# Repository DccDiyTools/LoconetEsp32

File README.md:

# LoconetEsp32
Esp32 Loconet Interface
# LocoBuffer from LocoLinx32U4

Board for use wiht the [https://github.com/mrrwa/LocoNet/tree/master/examples/LocoLinx32U4] code, there is a copy on this repository for platform.io .

# 0.0.1
- [x] USB
- [x] Loconet
- [x] Leds loconet
- [x] ESP32
- [ ] Btn Reset

# 0.0.X
- [] Loconet Power 
- [] Loconet Master
- [] USB-C
- [] Non-Inv TX
- [] SD
- [] BTN AP
- [] Led Wifi RGB

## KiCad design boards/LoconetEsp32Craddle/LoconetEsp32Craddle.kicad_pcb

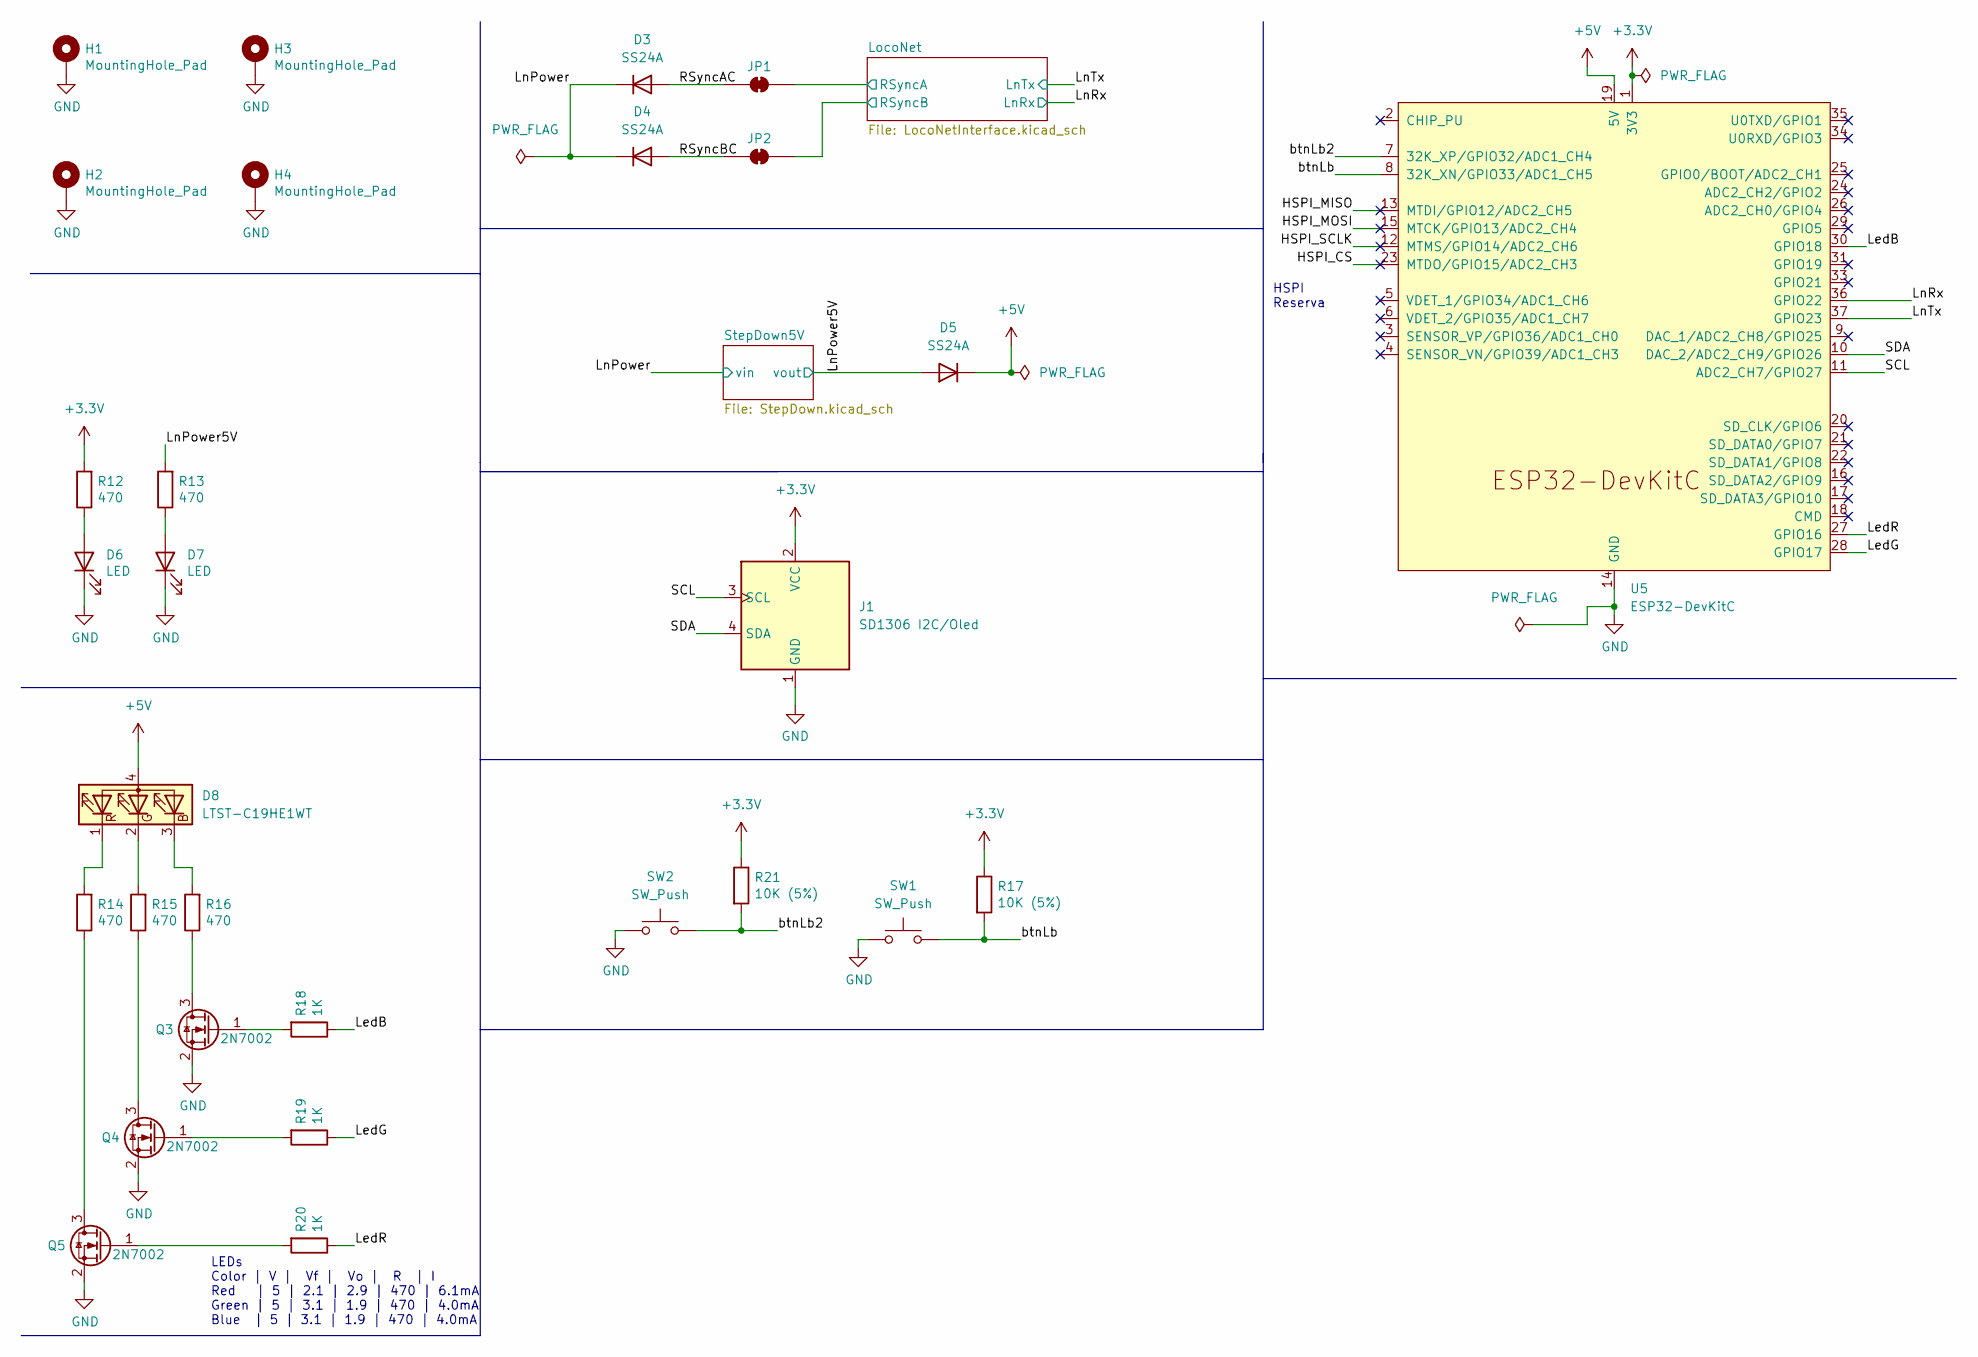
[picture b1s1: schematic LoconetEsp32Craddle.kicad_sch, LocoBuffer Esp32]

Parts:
D3, D4, D5: SS24A; D_SMA; LCSC C95872
D6, D7: LED; LED_0805_2012Metric; LCSC C2296
D8: LTST-C19HE1WT; LED_LiteOn_LTST-C19HE1WT; LCSC C458749
H1, H2, H3, H4: MountingHole_Pad; MountingHole_3.2mm_M3_ISO7380_Pad
J1: SD1306 I2C/Oled; ER_OLEDM0.91_1x-I2C-128x64OLED
JP1, JP2: SolderJumper_2_Bridged; SolderJumper-2_P1.3mm_Bridged2Bar_RoundedPad1.0x1.5mm
Q3, Q4, Q5: 2N7002; SOT-23; LCSC C8545
R12, R13, R14, R15, R16: 470; R_0805_2012Metric; LCSC C17710
R17, R21: 10K (5%); R_0805_2012Metric; LCSC C17414
R18, R19, R20: 1K; R_0805_2012Metric; LCSC C17513
SW1, SW2: SW_Push; SW_SPST_CK_RS282G05A3
U5: ESP32-DevKitC

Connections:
+3.3V: J1.2 (VCC), R12.2, R17.1, R21.1, U5.1 (3V3); also elsewhere on the board
+5V: D5.1 (K), D8.4 (A), U5.19 (5V)
/HSPI_CS: U5.23 (MTDO/GPIO15/ADC2_CH3)
/HSPI_MISO: U5.13 (MTDI/GPIO12/ADC2_CH5)
/HSPI_MOSI: U5.15 (MTCK/GPIO13/ADC2_CH4)
/HSPI_SCLK: U5.12 (MTMS/GPIO14/ADC2_CH6)
/LedB: R18.1, U5.30 (GPIO18)
/LedG: R19.1, U5.28 (GPIO17)
/LedR: R20.1, U5.27 (GPIO16)
/LnPower: D3.1 (K), D4.1 (K); also elsewhere on the board
/LnPower5V: D5.2 (A), R13.2; also elsewhere on the board
/LnRx: U5.36 (GPIO22); also elsewhere on the board
/LnTx: U5.37 (GPIO23); also elsewhere on the board
/LocoNet/RSyncA: JP1.2 (B); also elsewhere on the board
/LocoNet/RSyncB: JP2.2 (B); also elsewhere on the board
/RSyncAC: D3.2 (A), JP1.1 (A)
/RSyncBC: D4.2 (A), JP2.1 (A)
/SCL: J1.3 (SCL), U5.11 (ADC2_CH7/GPIO27)
/SDA: J1.4 (SDA), U5.10 (DAC_2/ADC2_CH9/GPIO26)
/btnLb: R17.2, SW1.2, U5.8 (32K_XN/GPIO33/ADC1_CH5)
/btnLb2: R21.2, SW2.2, U5.7 (32K_XP/GPIO32/ADC1_CH4)
GND: D6.1 (K), D7.1 (K), H1.1 (1_1), H2.1 (1_1), H3.1 (1_1), H4.1 (1_1), J1.1 (GND), Q3.2 (S), Q4.2 (S), Q5.2 (S), SW1.1, SW2.1, U5.14 (GND), U5.32 (GND), U5.38 (GND); also elsewhere on the board
unnamed: D6.2 (A), R12.1
unnamed: D7.2 (A), R13.1
unnamed: D8.3 (BK), R16.2
unnamed: D8.2 (GK), R15.2
unnamed: D8.1 (RK), R14.2
unnamed: Q3.3 (D), R16.1
unnamed: Q3.1 (G), R18.2
unnamed: Q4.3 (D), R15.1
unnamed: Q4.1 (G), R19.2
unnamed: Q5.3 (D), R14.1
unnamed: Q5.1 (G), R20.2

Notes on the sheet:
LEDs Color | V | Vf | Vo | R | I Red | 5 | 2.1 | 2.9 | 470 | 6.1mA Green | 5 | 3.1 | 1.9 | 470 | 4.0mA Blue | 5 | 3.1 | 1.9 | 470 | 4.0mA
HSPI Reserva

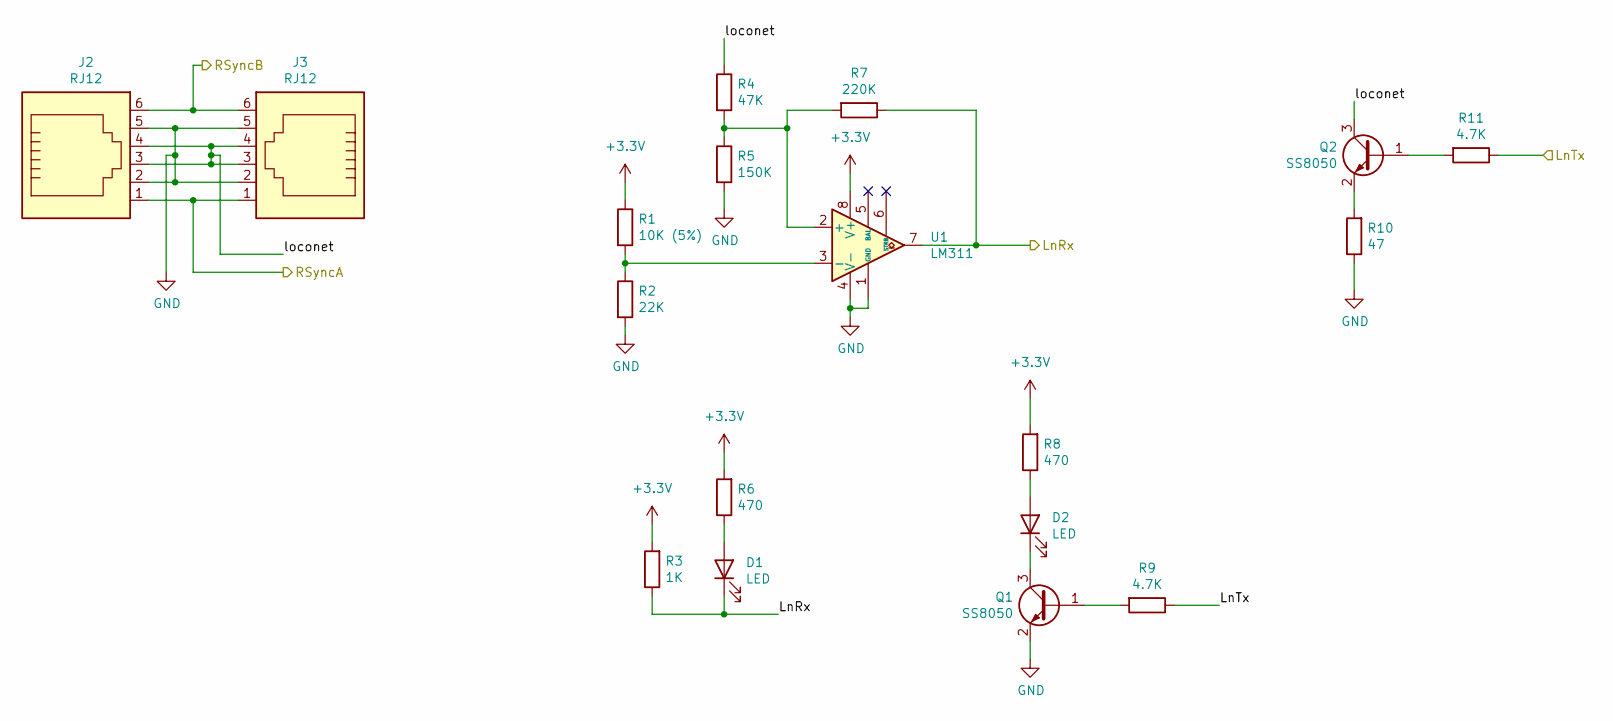
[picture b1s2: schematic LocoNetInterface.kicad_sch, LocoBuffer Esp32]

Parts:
D1, D2: LED; LED_0805_2012Metric; LCSC C2296
J2, J3: RJ12; RJ12_AMPHENOL_RJE0166001
Q1, Q2: SS8050; SOT-23; LCSC C2150
R1: 10K (5%); R_0805_2012Metric; LCSC C17414
R2: 22K; R_0805_2012Metric; LCSC C17560
R3: 1K; R_0805_2012Metric; LCSC C17513
R4: 47K; R_0805_2012Metric; LCSC C17713
R5: 150K; R_0805_2012Metric; LCSC C17470
R6, R8: 470; R_0805_2012Metric; LCSC C17710
R7: 220K; R_0805_2012Metric; LCSC C17556
R9, R11: 4.7K; R_0805_2012Metric; LCSC C229219
R10: 47; R_0805_2012Metric; LCSC C17714
U1: LM311; SOIC-8_3.9x4.9mm_P1.27mm; LCSC C12597

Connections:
+3.3V: R1.1, R3.2, R6.2, R8.2, U1.8 (V+); also elsewhere on the board
/LnRx: D1.1 (K), R3.1, R7.1, U1.7; also elsewhere on the board
/LnTx: R9.1, R11.1; also elsewhere on the board
/LocoNet/RSyncA: J2.1, J3.1; also elsewhere on the board
/LocoNet/RSyncB: J2.6, J3.6; also elsewhere on the board
/LocoNet/loconet: J2.3, J2.4, J3.3, J3.4, Q2.3 (C), R4.1
GND: J2.2, J2.5, J3.2, J3.5, Q1.2 (E), R2.2, R5.2, R10.1, U1.1 (GND), U1.4 (V-); also elsewhere on the board
unnamed: D1.2 (A), R6.1
unnamed: D2.2 (A), R8.1
unnamed: D2.1 (K), Q1.3 (C)
unnamed: Q1.1 (B), R9.2
unnamed: Q2.1 (B), R11.2
unnamed: Q2.2 (E), R10.2
unnamed: R4.2, R5.1, R7.2, U1.2 (+)
unnamed: R1.2, R2.1, U1.3 (-)

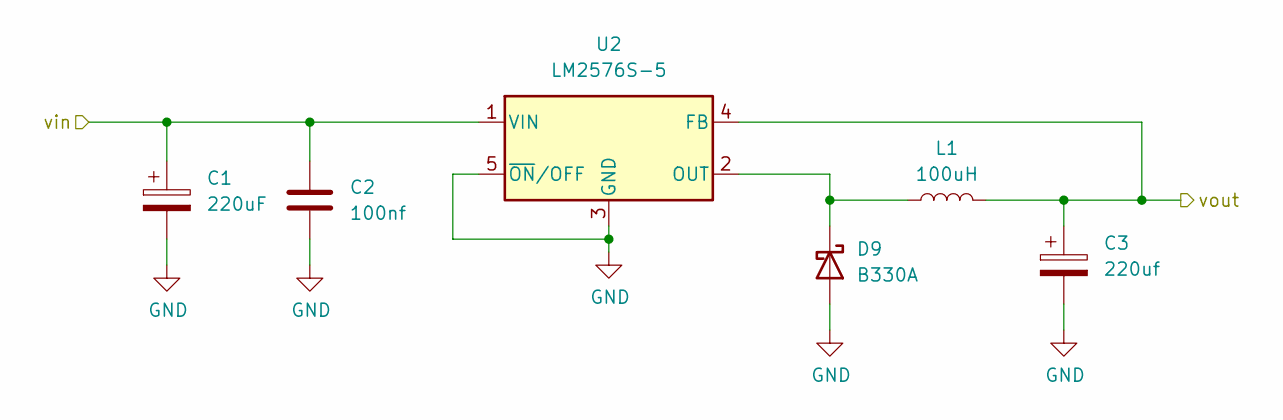
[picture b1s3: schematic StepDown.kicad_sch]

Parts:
C1: 220uF; CP_Elec_8x10.5; LCSC C131124
C2: 100nf; C_0805_2012Metric; LCSC C282732
C3: 220uf; CP_Elec_8x10.5; LCSC C131124
D9: B330A; D_SMA; LCSC C110485
L1: 100uH; L_Sunlord_MWSA1206S-101; LCSC C408533
U2: LM2576S-5; TO-263-5_TabPin3; LCSC C194472

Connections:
/LnPower: C1.1, C2.1, U2.1 (VIN); also elsewhere on the board
/LnPower5V: C3.1, L1.2, U2.4 (FB); also elsewhere on the board
GND: C1.2, C2.2, C3.2, D9.2 (A), U2.3 (GND), U2.5 (~ON/OFF); also elsewhere on the board
unnamed: D9.1 (K), L1.1, U2.2 (OUT)

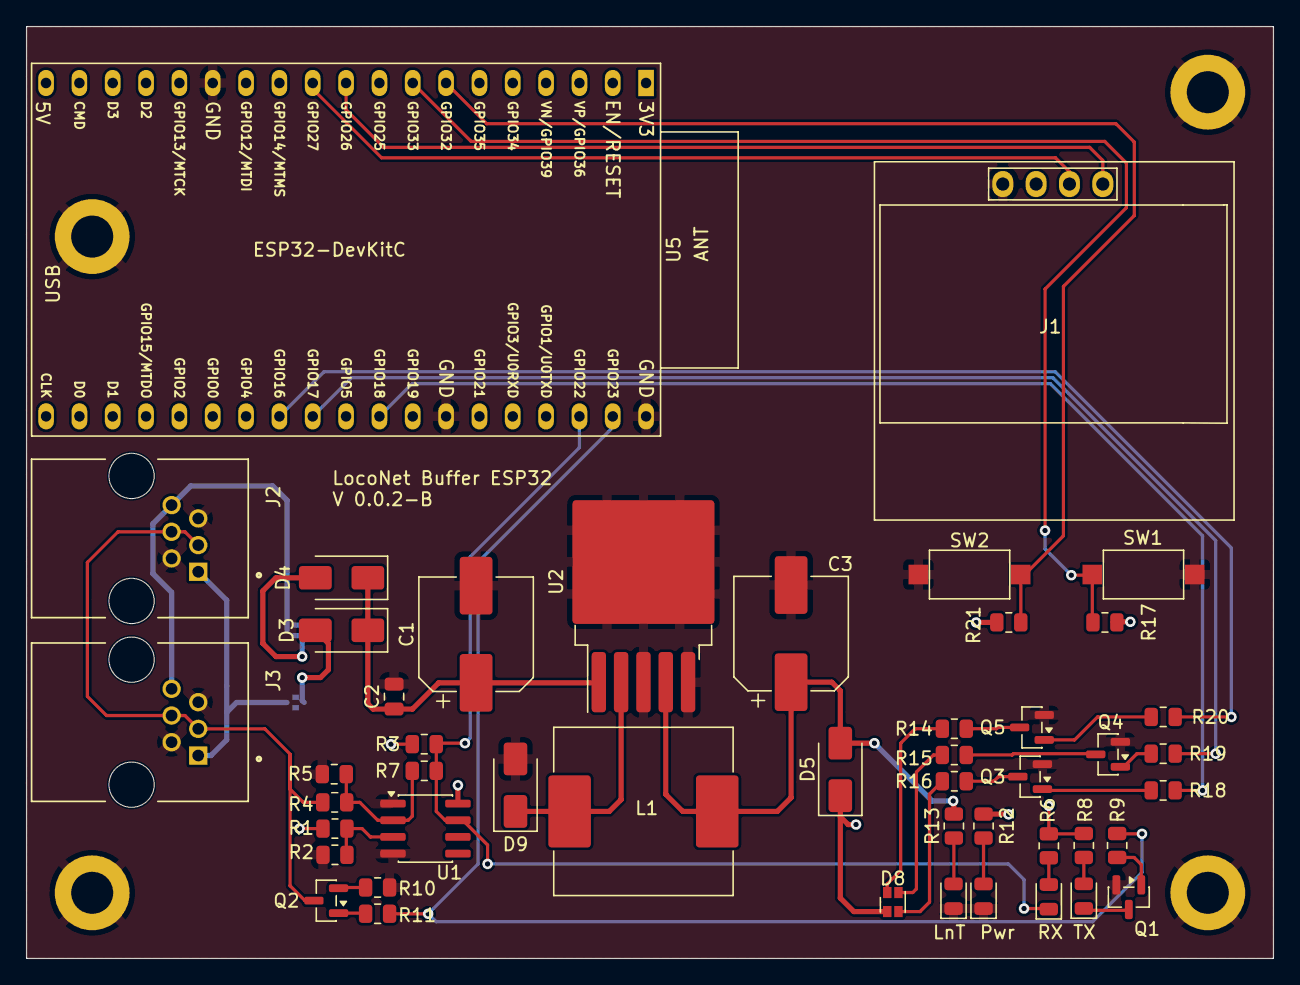
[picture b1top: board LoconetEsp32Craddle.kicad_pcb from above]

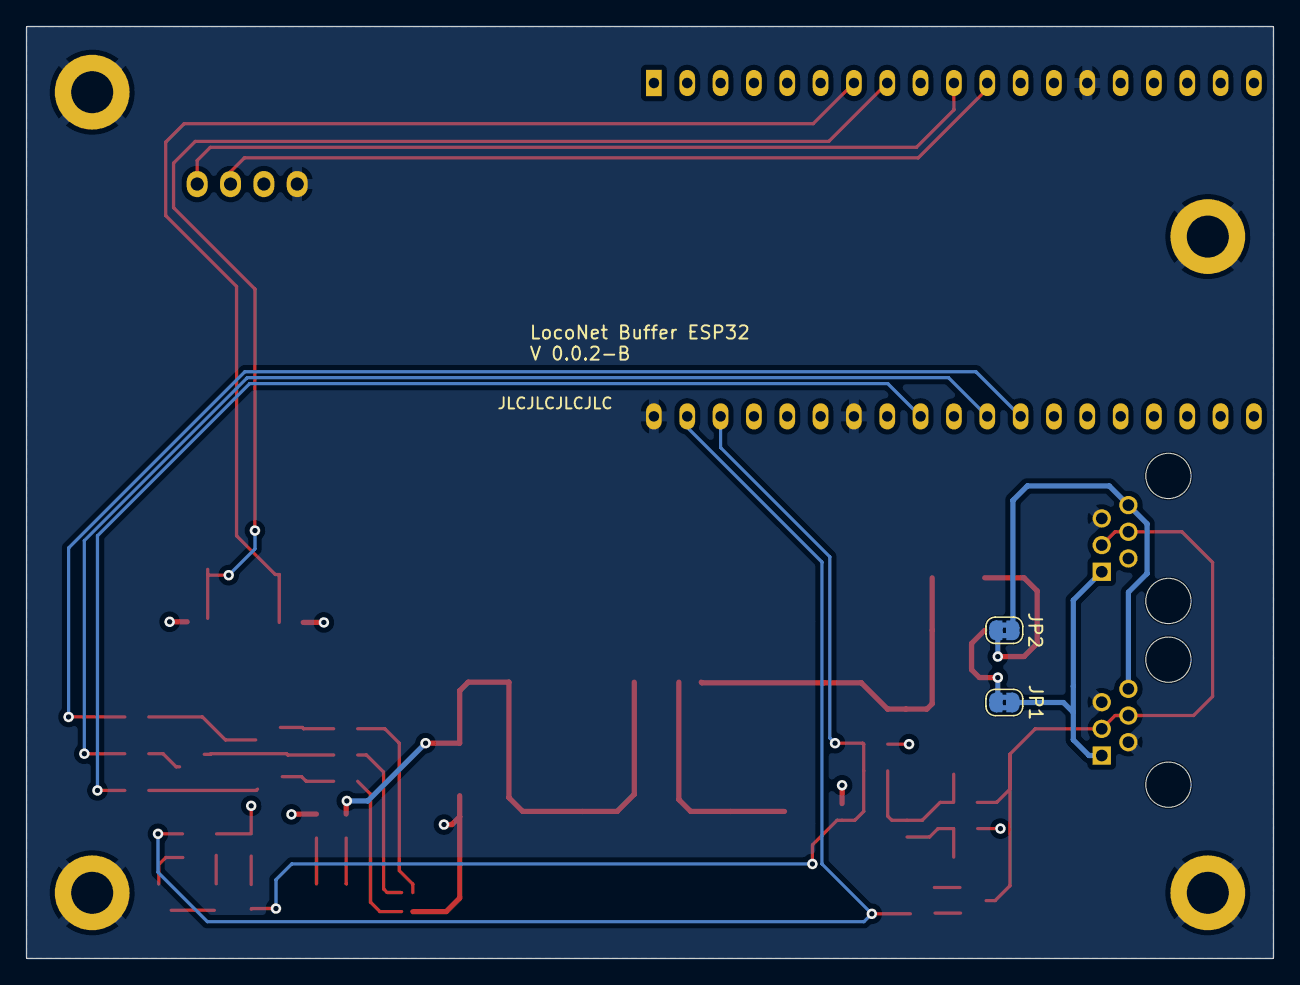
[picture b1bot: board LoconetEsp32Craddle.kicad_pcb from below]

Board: 4 copper layers, 95.0 x 71.0 mm, 53 parts (2 on the bottom side), 39 nets.

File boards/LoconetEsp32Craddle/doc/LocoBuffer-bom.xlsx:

|  | Bill of Materials
 |  | Schematic: | LocoBuffer | Component Groups: | 24
 |  | Variant: | default | Component Count: | 47 (43 SMD/ 4 THT)
 |  | Revision: | 0.0.1 | Fitted Components: | 47 (43 SMD/ 4 THT)
 |  | Date: | 2023-07-17 | Number of PCBs: | 1
 |  | KiCad Version: | 7.0.7-7.0.7~ubuntu23.04.1 | Total Components: | 47
Row | Description | Part | References | Value | Footprint | Quantity Per PCB | Status | Datasheet | LCSC | Sim.Device | Sim.Pins
1 | Unpolarized capacitor | C | C2 | 100nf | C_0805_2012Metric | 1 |  | ~ | C282732
2 | Polarized capacitor | C_Polarized | C1 C3 | 220uF | CP_Elec_8x10.5 | 2 |  | ~ | C131124
3 | 30V 3A Schottky Barrier Rectifier Diode, SMC | B330 | D9 | B330A | D_SMA | 1 |  | http://www.jameco.com/Jameco/Products/ProdDS/1538777.pdf | C110485
4 | Light emitting diode | LED | D1 D2 D6 D7 | LED | LED_0805_2012Metric | 4 |  | ~ | C2296
5 | RGB LED, red/green/blue/anode | LED_RGBA | D8 | LTST-C19HE1WT | LED_LiteOn_LTST-C19HE1WT | 1 |  | ~ | C458749
6 | Diode | D | D3 D4 D5 | SS24A | D_SMA | 3 |  | ~ | C95872 | D | 1=K 2=A
7 | RJ connector, 6P6C (6 positions 6 connected) | RJ12 | J2 J3 | RJ12 | AMPHENOL_RJE0166001 | 2 |  | ~
8 | Generic connector, single row, 01x04, script generated (kicad-library-utils/sch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 | Conn_01x04 | J1 | SD1306 I2C/Oled | 128x64OLED | 1 |  | ~
9 | Inductor | L | L1 | 100uH | L_Sunlord_MWSA1206S-101 | 1 |  | ~ | C408533
10 | 0.115A Id, 60V Vds, N-Channel MOSFET, SOT-23 | 2N7002 | Q3 Q4 Q5 | 2N7002 | SOT-23 | 3 |  | https://www.onsemi.com/pub/Collateral/NDS7002A-D.PDF | C8545
11 | NPN transistor, base/emitter/collector | Q_NPN_BEC | Q1 Q2 | SS8050 | SOT-23 | 2 |  | ~ | C2150
12 | Resistor | R | R10 | 47 | R_0805_2012Metric | 1 |  | ~ | C17714
13 | Resistor | R | R6 R8 R12 R13 R14 R15 R16 | 470 | R_0805_2012Metric | 7 |  | ~ | C17710
14 | Resistor | R | R3 R18 R19 R20 | 1K | R_0805_2012Metric | 4 |  | ~ | C17513
15 | Resistor | R | R9 R11 | 4.7K | R_0805_2012Metric | 2 |  | ~ | C229219
16 | Resistor | R | R2 | 22K | R_0805_2012Metric | 1 |  | ~ | C17560
17 | Resistor | R | R4 | 47K | R_0805_2012Metric | 1 |  | ~ | C17713
18 | Resistor | R | R5 | 150K | R_0805_2012Metric | 1 |  | ~ | C17470
19 | Resistor | R | R7 | 220K | R_0805_2012Metric | 1 |  | ~ | C17556
20 | Resistor | R | R1 R17 R21 | 10K (5%) | R_0805_2012Metric | 3 |  | ~ | C17414
21 | Push button switch, generic, two pins | SW_Push | SW1 SW2 | SW_Push | SW_SPST_CK_RS282G05A3 | 2 |  | ~
22 | Development Kit | ESP32-DevKitC | U5 | ESP32-DevKitC | ESP32-DevKitC | 1 |  | https://docs.espressif.com/projects/esp-idf/zh_CN/latest/esp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
23 | 5V, 3A SIMPLE SWITCHER® Step-Down Voltage Regulator, TO-263 | LM2576S-5 | U2 | LM2576S-5 | TO-263-5_TabPin3 | 1 |  | http://www.ti.com/lit/ds/symlink/lm2576.pdf | C194472
24 | Voltage Comparator, DIP-8/SOIC-8 | LM311 | U1 | LM311 | SOIC-8_3.9x4.9mm_P1.27mm | 1 |  | http://www.ti.com/lit/ds/symlink/lm311.pdf | C12597

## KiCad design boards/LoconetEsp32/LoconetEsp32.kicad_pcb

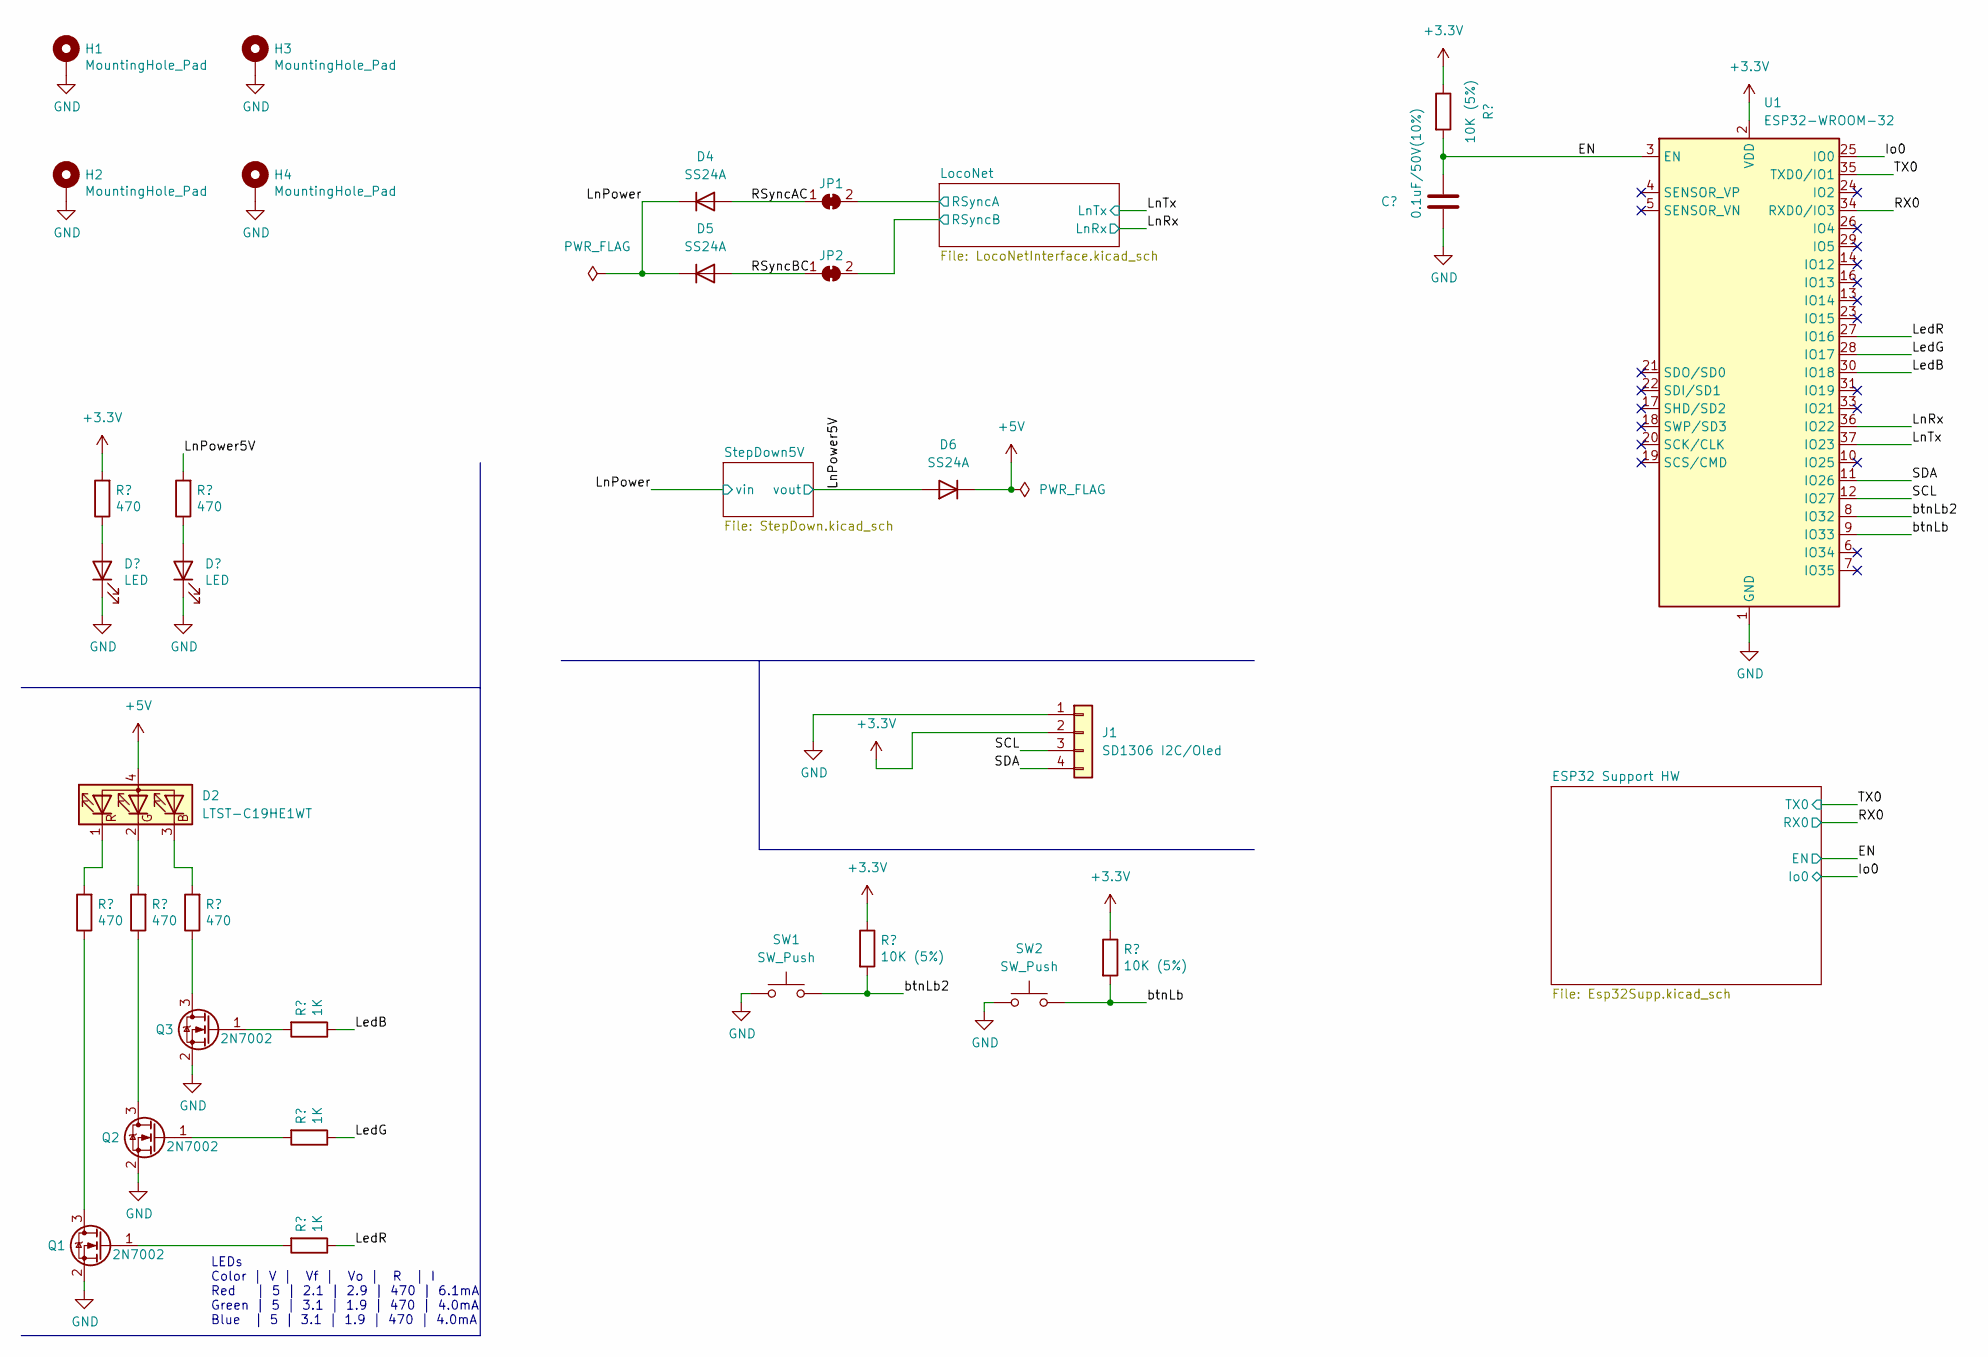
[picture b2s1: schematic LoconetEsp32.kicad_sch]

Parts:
C1: 0.1uF/50V(10%); C_0805_2012Metric; LCSC C49678
D1, D3: LED; LED_0805_2012Metric; LCSC C2296
D2: LTST-C19HE1WT; LED_LiteOn_LTST-C19HE1WT; LCSC C458749
D4, D5, D6: SS24A; D_SMA; LCSC C95872
H1, H2, H3, H4: MountingHole_Pad; MountingHole_3.2mm_M3_ISO7380_Pad
J1: SD1306 I2C/Oled; 128x64OLED
JP1, JP2: SolderJumper_2_Bridged; SolderJumper-2_P1.3mm_Bridged2Bar_RoundedPad1.0x1.5mm
Q1, Q2, Q3: 2N7002; SOT-23; LCSC C8545
R1, R2, R3, R4, R5: 470; R_0805_2012Metric; LCSC C17710
R6, R7, R8: 1K; R_0805_2012Metric; LCSC C17513
R9, R10, R11: 10K (5%); R_0805_2012Metric; LCSC C17414
SW1, SW2: SW_Push; SW_SPST_CK_RS282G05A3
U1: ESP32-WROOM-32; LCSC C701343

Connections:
+3.3V: J1.2, R2.2, R9.1, R10.1, R11.1, U1.2 (VDD); also elsewhere on the board
+5V: D2.4 (A), D6.1 (K); also elsewhere on the board
/EN: C1.1, R11.2, U1.3 (EN); also elsewhere on the board
/Io0: U1.25 (IO0); also elsewhere on the board
/LedB: R6.1, U1.30 (IO18)
/LedG: R7.1, U1.28 (IO17)
/LedR: R8.1, U1.27 (IO16)
/LnPower: D4.1 (K), D5.1 (K); also elsewhere on the board
/LnPower5V: D6.2 (A), R4.2; also elsewhere on the board
/LnRx: U1.36 (IO22); also elsewhere on the board
/LnTx: U1.37 (IO23); also elsewhere on the board
/LocoNet/RSyncA: JP1.2 (B); also elsewhere on the board
/LocoNet/RSyncB: JP2.2 (B); also elsewhere on the board
/RSyncAC: D4.2 (A), JP1.1 (A)
/RSyncBC: D5.2 (A), JP2.1 (A)
/RX0: U1.34 (RXD0/IO3); also elsewhere on the board
/SCL: J1.3, U1.12 (IO27)
/SDA: J1.4, U1.11 (IO26)
/TX0: U1.35 (TXD0/IO1); also elsewhere on the board
/btnLb: R10.2, SW2.2, U1.9 (IO33)
/btnLb2: R9.2, SW1.2, U1.8 (IO32)
GND: C1.2, D1.1 (K), D3.1 (K), H1.1, H2.1, H3.1, H4.1, J1.1, Q1.2 (S), Q2.2 (S), Q3.2 (S), SW1.1, SW2.1, U1.1 (GND), U1.15 (GND), U1.38 (GND), U1.39 (GND); also elsewhere on the board
unnamed: D1.2 (A), R2.1
unnamed: D2.3 (BK), R5.2
unnamed: D2.2 (GK), R3.2
unnamed: D2.1 (RK), R1.2
unnamed: D3.2 (A), R4.1
unnamed: Q1.3 (D), R1.1
unnamed: Q1.1 (G), R8.2
unnamed: Q2.3 (D), R3.1
unnamed: Q2.1 (G), R7.2
unnamed: Q3.3 (D), R5.1
unnamed: Q3.1 (G), R6.2

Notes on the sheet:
LEDs Color | V | Vf | Vo | R | I Red | 5 | 2.1 | 2.9 | 470 | 6.1mA Green | 5 | 3.1 | 1.9 | 470 | 4.0mA Blue | 5 | 3.1 | 1.9 | 470 | 4.0mA

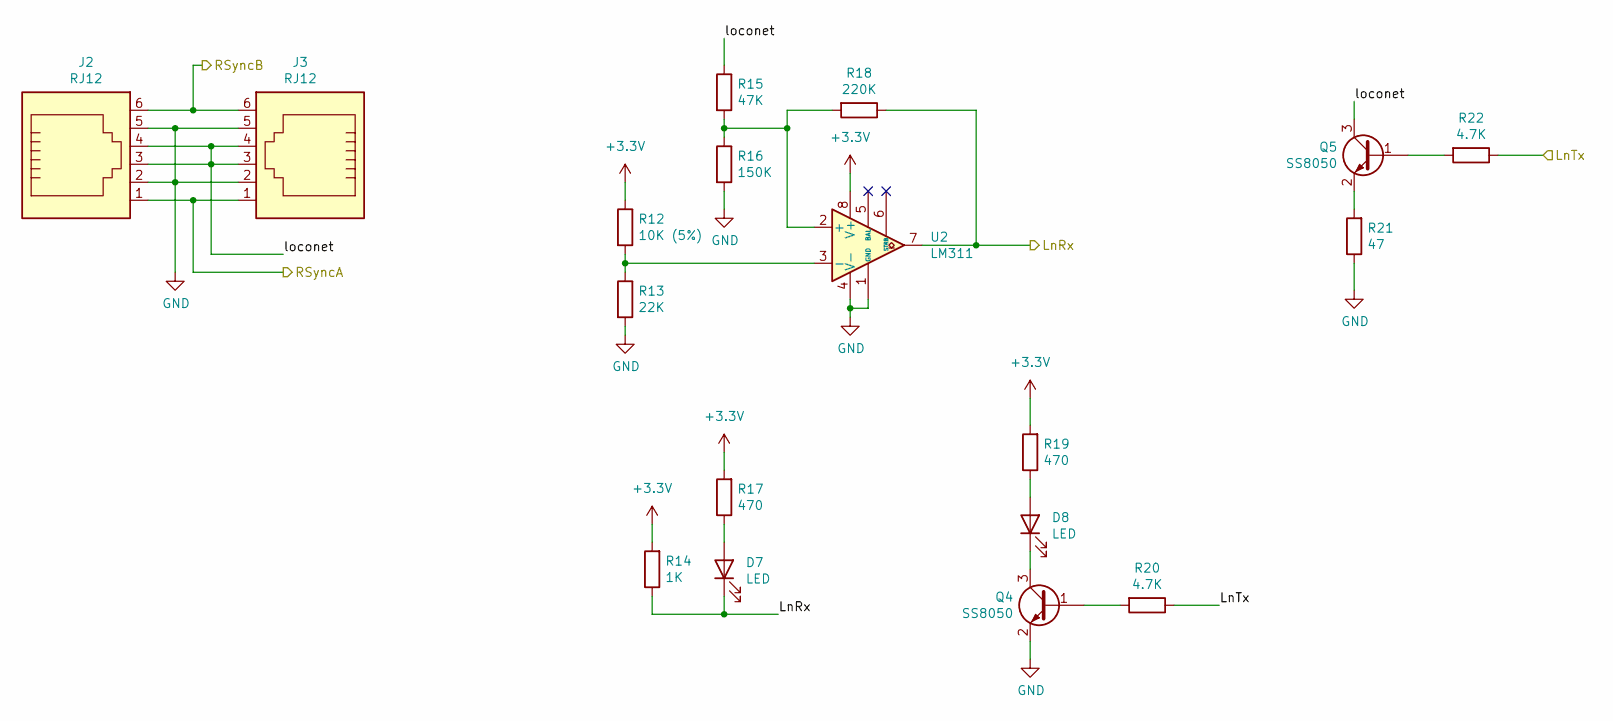
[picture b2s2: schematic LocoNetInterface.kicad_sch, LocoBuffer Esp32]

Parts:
D7, D8: LED; LED_0805_2012Metric; LCSC C2296
J2, J3: RJ12; AMPHENOL_RJE0166001
Q4, Q5: SS8050; SOT-23; LCSC C2150
R12: 10K (5%); R_0805_2012Metric; LCSC C17414
R13: 22K; R_0805_2012Metric; LCSC C17560
R14: 1K; R_0805_2012Metric; LCSC C17513
R15: 47K; R_0805_2012Metric; LCSC C17713
R16: 150K; R_0805_2012Metric; LCSC C17470
R17, R19: 470; R_0805_2012Metric; LCSC C17710
R18: 220K; R_0805_2012Metric; LCSC C17556
R20, R22: 4.7K; R_0805_2012Metric; LCSC C229219
R21: 47; R_0805_2012Metric; LCSC C17714
U2: LM311; SOIC-8_3.9x4.9mm_P1.27mm; LCSC C12597

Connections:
+3.3V: R12.1, R14.2, R17.2, R19.2, U2.8 (V+); also elsewhere on the board
/LnRx: D7.1 (K), R14.1, R18.1, U2.7; also elsewhere on the board
/LnTx: R20.1, R22.1; also elsewhere on the board
/LocoNet/RSyncA: J2.1, J3.1; also elsewhere on the board
/LocoNet/RSyncB: J2.6, J3.6; also elsewhere on the board
/LocoNet/loconet: J2.3, J2.4, J3.3, J3.4, Q5.3 (C), R15.1
GND: J2.2, J2.5, J3.2, J3.5, Q4.2 (E), R13.2, R16.2, R21.1, U2.1 (GND), U2.4 (V-); also elsewhere on the board
unnamed: D7.2 (A), R17.1
unnamed: D8.2 (A), R19.1
unnamed: D8.1 (K), Q4.3 (C)
unnamed: Q4.1 (B), R20.2
unnamed: Q5.1 (B), R22.2
unnamed: Q5.2 (E), R21.2
unnamed: R15.2, R16.1, R18.2, U2.2 (+)
unnamed: R12.2, R13.1, U2.3 (-)

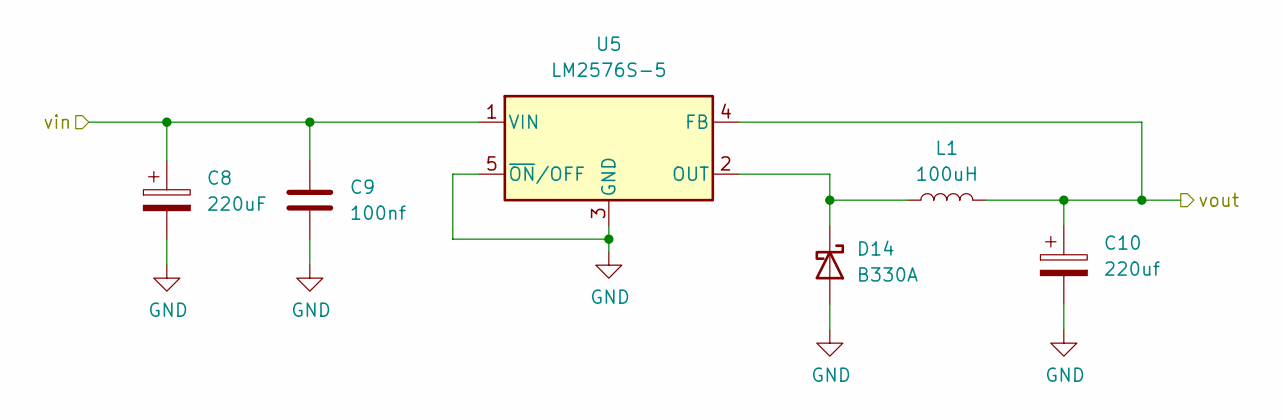
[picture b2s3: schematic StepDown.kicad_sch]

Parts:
C8: 220uF; CP_Elec_8x10.5; LCSC C131124
C9: 100nf; C_0805_2012Metric; LCSC C282732
C10: 220uf; CP_Elec_8x10.5; LCSC C131124
D14: B330A; D_SMA; LCSC C110485
L1: 100uH; L_Sunlord_MWSA1206S-101; LCSC C408533
U5: LM2576S-5; TO-263-5_TabPin3; LCSC C194472

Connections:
/LnPower: C8.1, C9.1, U5.1 (VIN); also elsewhere on the board
/LnPower5V: C10.1, L1.2, U5.4 (FB); also elsewhere on the board
GND: C8.2, C9.2, C10.2, D14.2 (A), U5.3 (GND), U5.5 (~ON/OFF); also elsewhere on the board
unnamed: D14.1 (K), L1.1, U5.2 (OUT)

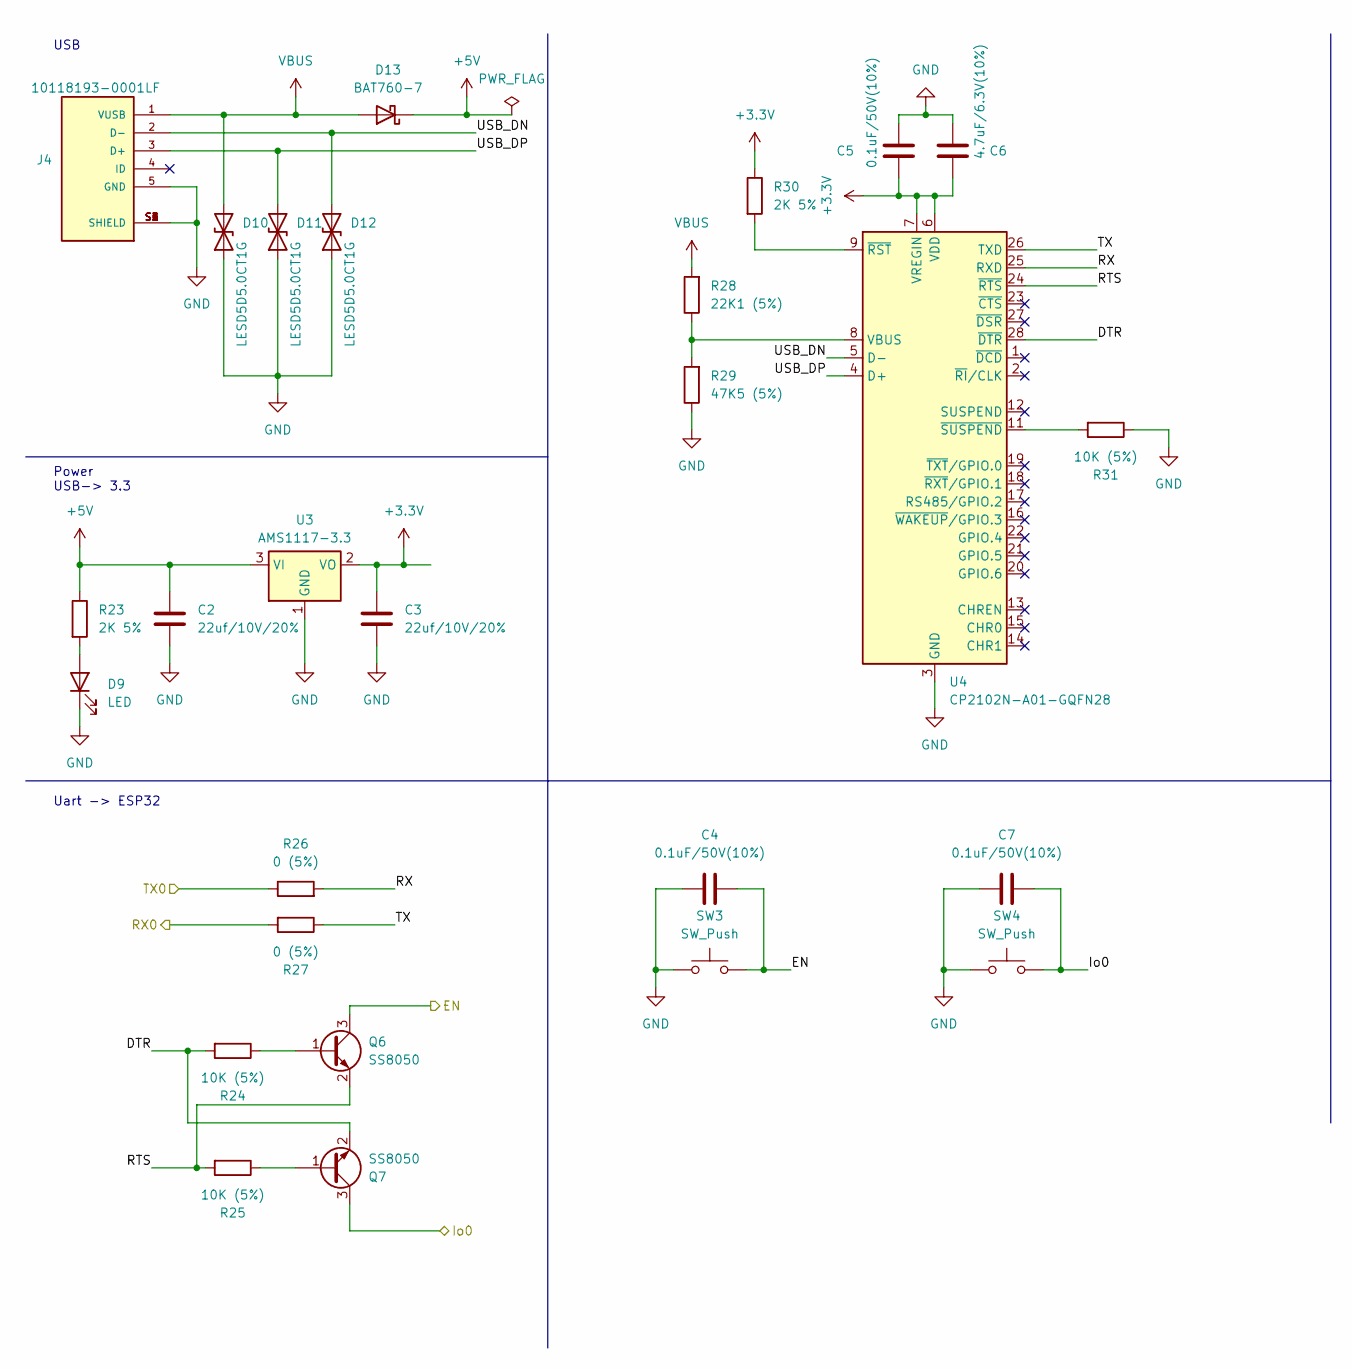
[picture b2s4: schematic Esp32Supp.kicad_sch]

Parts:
C2, C3: 22uf/10V/20%; C_0805_2012Metric; LCSC C45783
C4, C5, C7: 0.1uF/50V(10%); C_0805_2012Metric; LCSC C49678
C6: 4.7uF/6.3V(10%); C_0805_2012Metric; LCSC C1779
D9: LED; LED_0805_2012Metric; LCSC C2296
D10, D11, D12: LESD5D5.0CT1G; D_SOD-523; LCSC C383211
D13: BAT760-7; D_SOD-323; LCSC C124187
J4: 10118193-0001LF; AMPHENOL_10118193-0001LF; PARTREV E; LCSC C132562
Q6, Q7: SS8050; SOT-23; LCSC C2150
R23, R30: 2K 5%; R_0805_2012Metric; LCSC C212449
R24, R25, R31: 10K (5%); R_0805_2012Metric; LCSC C17414
R26, R27: 0 (5%); R_0805_2012Metric; LCSC C2936632
R28: 22K1 (5%); R_0805_2012Metric; LCSC C153391
R29: 47K5 (5%); R_0805_2012Metric; LCSC C245335
SW3, SW4: SW_Push; SW_SPST_CK_RS282G05A3
U3: AMS1117-3.3; SOT-223-3_TabPin2; LCSC C6186
U4: CP2102N-A01-GQFN28; QFN-28-1EP_5x5mm_P0.5mm_EP3.35x3.35mm; LCSC C964632

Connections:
+3.3V: C3.1, C5.2, C6.2, R30.1, U3.2 (VO), U4.6 (VDD), U4.7 (VREGIN); also elsewhere on the board
+5V: C2.1, D13.1 (K), R23.1, U3.3 (VI); also elsewhere on the board
/EN: C4.2, Q6.3 (C), SW3.2; also elsewhere on the board
/ESP32 Support HW/DTR: Q7.2 (E), R24.2, U4.28 (~DTR)
/ESP32 Support HW/RTS: Q6.2 (E), R25.2, U4.24 (~RTS)
/ESP32 Support HW/RX: R26.2, U4.25 (RXD)
/ESP32 Support HW/TX: R27.1, U4.26 (TXD)
/ESP32 Support HW/USB_DN: D12.2 (A2), J4.2 (D-), U4.5 (D-)
/ESP32 Support HW/USB_DP: D11.2 (A2), J4.3 (D+), U4.4 (D+)
/Io0: C7.2, Q7.3 (C), SW4.2; also elsewhere on the board
/RX0: R27.2; also elsewhere on the board
/TX0: R26.1; also elsewhere on the board
GND: C2.2, C3.2, C4.1, C5.1, C6.1, C7.1, D9.1 (K), D10.1 (A1), D11.1 (A1), D12.1 (A1), J4.5 (GND), J4.S1 (SHIELD), J4.S2 (SHIELD), J4.S3 (SHIELD), J4.S4 (SHIELD), J4.S5 (SHIELD), J4.S6 (SHIELD), R29.1, R31.1, SW3.1, SW4.1, U3.1 (GND), U4.3 (GND), U4.29 (GND); also elsewhere on the board
unnamed: D9.2 (A), R23.2
unnamed: Q6.1 (B), R24.1
unnamed: Q7.1 (B), R25.1
unnamed: R28.1, R29.2, U4.8 (VBUS)
unnamed: R30.2, U4.9 (~RST)
unnamed: R31.2, U4.11 (~SUSPEND)
VBUS: D10.2 (A2), D13.2 (A), J4.1 (VUSB), R28.2

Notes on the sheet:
Power USB-> 3.3
Uart -> ESP32
USB
